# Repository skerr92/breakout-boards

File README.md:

# breakout-boards
Repository for various breakout board schematics, board files, and Bill of Materials

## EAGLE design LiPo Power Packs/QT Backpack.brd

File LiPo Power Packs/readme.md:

# power pack boards and schematics

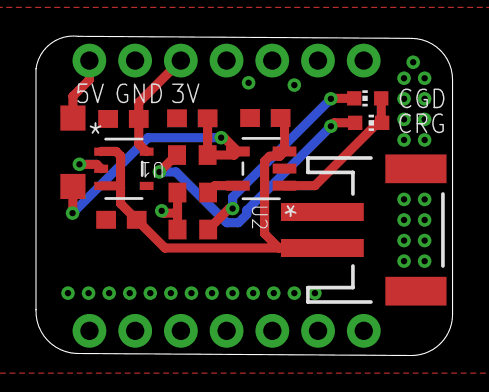
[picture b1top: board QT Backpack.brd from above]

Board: 2 copper layers, 23.1 x 17.8 mm, 15 parts (0 on the bottom side), 9 nets.

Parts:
C1: 0.47uF; C0603
C2: 1uF; C0603
C3, C4: 10uF; C0603
CGD: CHIP-LED0603
CRG: CHIP-LED0603
J1, J2: 1X07_NO_SILK
J3: JST-2-SMD
R1, R2: 470; R0603
R3: 2K; R0603
U1: TLV75533PDBVRDBV5_TEX-L; DBV5_TEX-L
U2: MCP73831T-2ACI/OT; SOT-23-5_MC
U$1: MBR0520LT1G; SOD3716X117(SOD-123)

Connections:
3V: C1.1, J1.5, U1.5
+5V: C4.1, R1.2, U2.4, U$1.2
GND: C1.2, C2.2, C3.2, C4.2, J1.6, J3.1, R2.1, R3.2, U1.2, U2.2
unnamed: R3.1, U2.5
unnamed: CGD.A, CRG.C, U2.1
unnamed: CGD.C, R2.2
unnamed: CRG.A, R1.1
VBAT: C2.1, C3.1, J3.2, U1.1, U1.3, U2.3
VUSB: J1.7, U$1.1

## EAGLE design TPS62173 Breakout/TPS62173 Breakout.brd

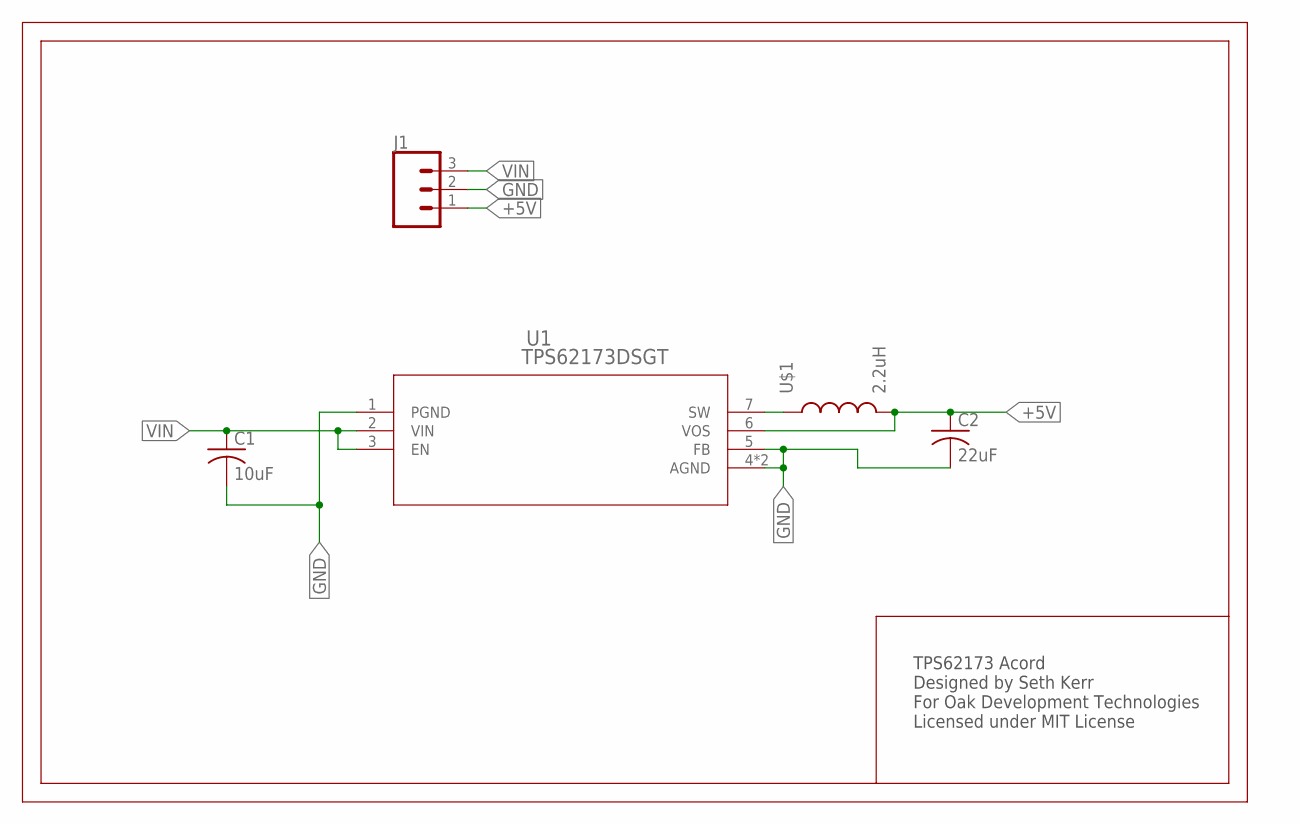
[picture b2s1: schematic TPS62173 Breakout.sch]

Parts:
C1: 10uF; C0603
C2: 22uF; C0603
J1: CONN_031X03_NO_SILK; 1X03_NO_SILK
U1: TPS62173DSGT; DSG8_1P6X0P9_TEX
U$1: 2.2uH; 2.7X3MM

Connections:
+5V: C2.1, J1.1, U1.6 (VOS), U$1.2
GND: C1.2, C2.2, J1.2, U1.1 (PGND), U1.4 (AGND), U1.5 (FB), U1.9 (AGND)
unnamed: U1.7 (SW), U$1.1
VIN: C1.1, J1.3, U1.2 (VIN), U1.3 (EN)

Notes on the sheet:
TPS62173 Acord Designed by Seth Kerr For Oak Development Technologies Licensed under MIT License

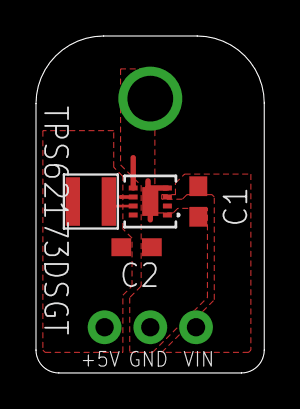
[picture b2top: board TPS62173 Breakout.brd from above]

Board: 2 copper layers, 12.7 x 18.7 mm, 5 parts (0 on the bottom side), 4 nets.

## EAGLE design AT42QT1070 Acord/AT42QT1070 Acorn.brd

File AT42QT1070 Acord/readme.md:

# AT42QT1070 acord schematics and board files

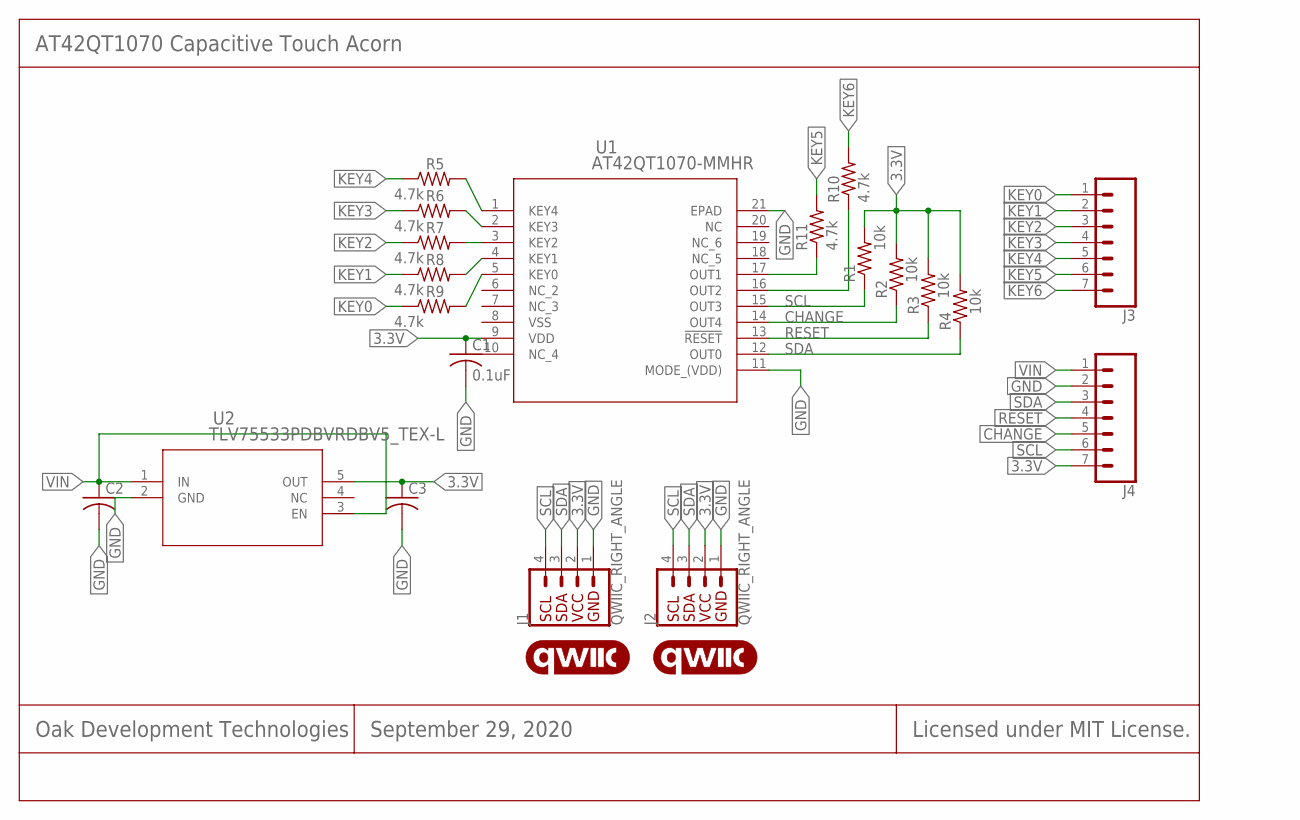
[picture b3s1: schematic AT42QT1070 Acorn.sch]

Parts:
C1: 0.1uF; C0402
C2, C3: C-USC0402; C0402
J1, J2: QWIIC_RIGHT_ANGLE; JST04_1MM_RA
J3, J4: CONN_07NO_SILK; 1X07_NO_SILK
LOGO1, LOGO2: QWIIC_LOGO_6MM; QWIIC_6MM
R1, R2, R3, R4: 10k; R0402
R5, R6, R7, R8, R9, R10, R11: 4.7k; R0402
U1: AT42QT1070-MMHR; VQFN20_3X3_MCH
U2: TLV75533PDBVRDBV5_TEX-L; DBV5_TEX-L

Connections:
3.3V: C1.1, C3.1, J1.2, J2.2, J4.7, R1.2, R2.2, R3.2, R4.2, U1.9 (VDD), U2.5 (OUT)
CHANGE: J4.5, R2.1, U1.14 (OUT4)
GND: C1.2, C2.2, C3.2, J1.1, J2.1, J4.2, U1.11 (MODE_(VDD)), U1.21 (EPAD), U2.2 (GND)
KEY0: J3.1, R9.1
KEY1: J3.2, R8.1
KEY2: J3.3, R7.1
KEY3: J3.4, R6.1
KEY4: J3.5, R5.1
KEY5: J3.6, R11.2
KEY6: J3.7, R10.2
unnamed: R11.1, U1.17 (OUT1)
unnamed: R10.1, U1.16 (OUT2)
unnamed: R5.2, U1.1 (KEY4)
unnamed: R6.2, U1.2 (KEY3)
unnamed: R7.2, U1.3 (KEY2)
unnamed: R8.2, U1.4 (KEY1)
unnamed: R9.2, U1.5 (KEY0)
RESET: J4.4, R3.1, U1.13 (!RESET)
SCL: J1.4, J2.4, J4.6, R1.1, U1.15 (OUT3)
SDA: J1.3, J2.3, J4.3, R4.1, U1.12 (OUT0)
VIN: C2.1, J4.1, U2.1 (IN), U2.3 (EN)

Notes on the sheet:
AT42QT1070 Capacitive Touch Acorn
Oak Development Technologies
Licensed under MIT License.
September 29, 2020

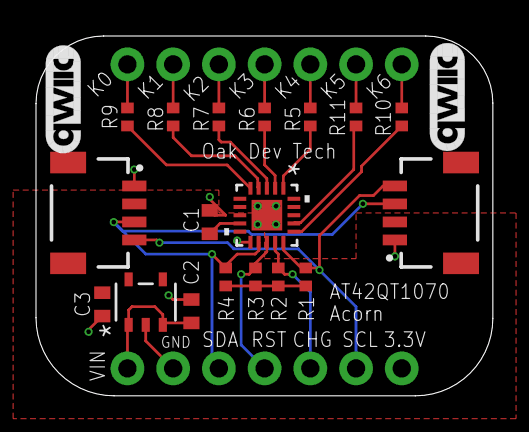
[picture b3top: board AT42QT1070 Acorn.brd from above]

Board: 2 copper layers, 25.4 x 20.0 mm, 22 parts (0 on the bottom side), 21 nets.

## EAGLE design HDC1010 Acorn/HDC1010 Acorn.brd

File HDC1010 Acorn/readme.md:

# HDC1010 Acorn

See MIT License in parent directory

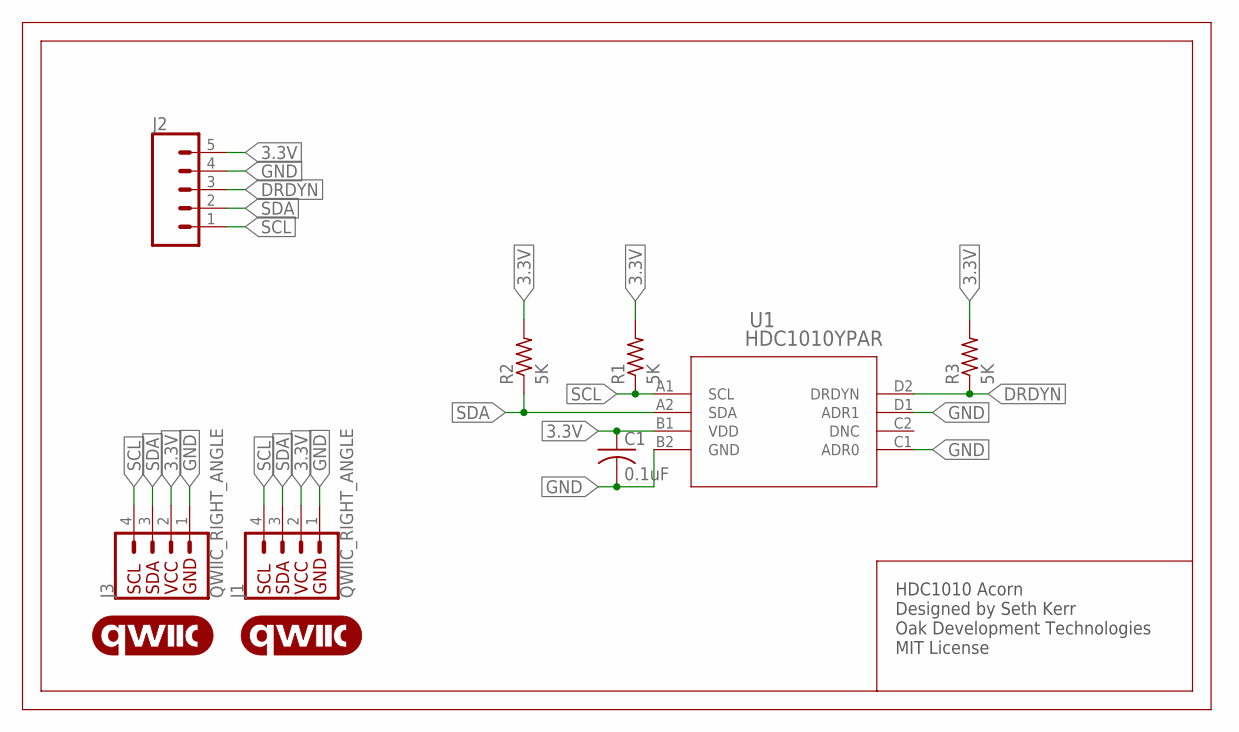
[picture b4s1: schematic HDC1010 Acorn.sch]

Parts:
C1: 0.1uF; C0402
J1, J3: QWIIC_RIGHT_ANGLE; JST04_1MM_RA
J2: CONN_05NO_SILK; 1X05_NO_SILK
LOGO1, LOGO2: QWIIC_LOGO_3MM; QWIIC_3MM
R1, R2, R3: 5K; R0603
U1: HDC1010YPAR; YPA8_TEX

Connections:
3.3V: C1.1, J1.2, J2.5, J3.2, R1.2, R2.2, R3.2, U1.B1 (VDD)
DRDYN: J2.3, R3.1, U1.D2 (DRDYN)
GND: C1.2, J1.1, J2.4, J3.1, U1.B2 (GND), U1.C1 (ADR0), U1.D1 (ADR1)
SCL: J1.4, J2.1, J3.4, R1.1, U1.A1 (SCL)
SDA: J1.3, J2.2, J3.3, R2.1, U1.A2 (SDA)

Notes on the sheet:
HDC1010 Acorn Designed by Seth Kerr Oak Development Technologies MIT License

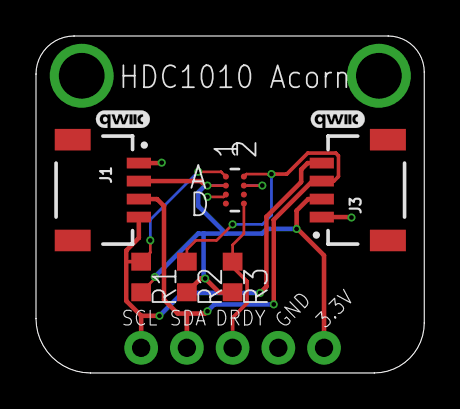
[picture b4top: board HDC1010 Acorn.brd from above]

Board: 2 copper layers, 21.6 x 18.7 mm, 10 parts (1 on the bottom side), 5 nets.

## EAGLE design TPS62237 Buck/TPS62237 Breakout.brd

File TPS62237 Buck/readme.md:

# TPS62237 3.3V Buck/Step Down converter board

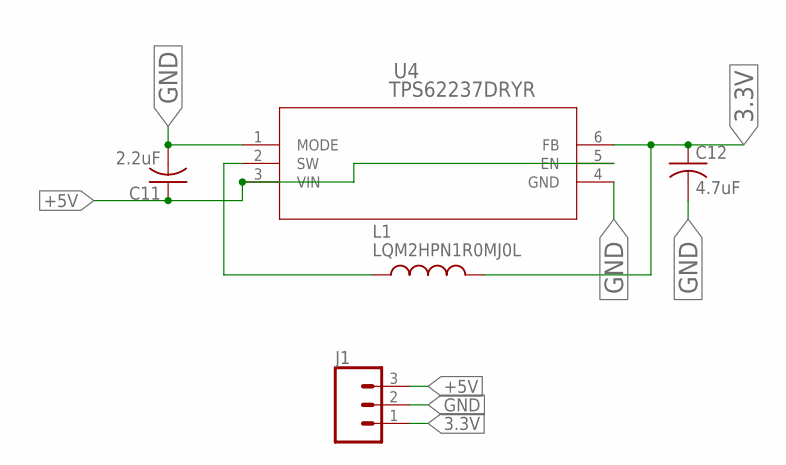
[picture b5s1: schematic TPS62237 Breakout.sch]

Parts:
C11: 2.2uF; C0603
C12: 4.7uF; C0603
J1: CONN_031X03_NO_SILK; 1X03_NO_SILK
L1: LQM2HPN1R0MJ0L; INDC2520X120N
U4: TPS62237DRYR; DRY6_TEX

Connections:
3.3V: C12.1, J1.1, L1.2, U4.6 (FB)
+5V: C11.1, J1.3, U4.3 (VIN), U4.5 (EN)
GND: C11.2, C12.2, J1.2, U4.1 (MODE), U4.4 (GND)
unnamed: L1.1, U4.2 (SW)

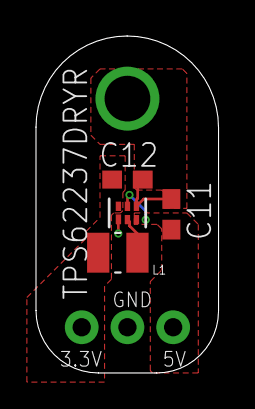
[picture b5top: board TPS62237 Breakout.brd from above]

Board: 2 copper layers, 10.1 x 18.7 mm, 5 parts (0 on the bottom side), 4 nets.

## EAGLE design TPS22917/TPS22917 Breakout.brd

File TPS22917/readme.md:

# TPS22917 Power Switch/ Load Switch IC breakout board.

Follow this <a href="https://www.oakdev.tech/tutorials-new-products/tutorial-getting-started-with-the-tps22917-load-switch-from-texas-instruments#/">LINK</a> to learn how to get started using this board.

# Buy the assembled board:

<a href="https://www.oakdev.tech/store/p1/TPS22917-Breakout.html#/">Buy the TPS22917 breakout here</a>

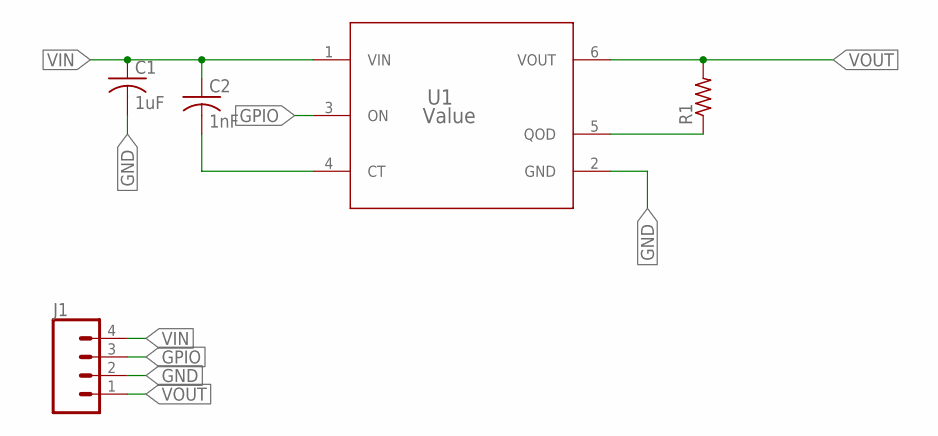
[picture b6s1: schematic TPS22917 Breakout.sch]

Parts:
C1: 1uF; C0603
C2: 1nF; C0603
J1: CONN_041X04_NO_SILK; 1X04_NO_SILK
R1: R-US_R0603; R0603
U1: Value; DBV0006_L

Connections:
GND: C1.2, J1.2, U1.2 (GND)
GPIO: J1.3, U1.3 (ON)
unnamed: C2.2, U1.4 (CT)
unnamed: R1.1, U1.5 (QOD)
VIN: C1.1, C2.1, J1.4, U1.1 (VIN)
VOUT: J1.1, R1.2, U1.6 (VOUT)

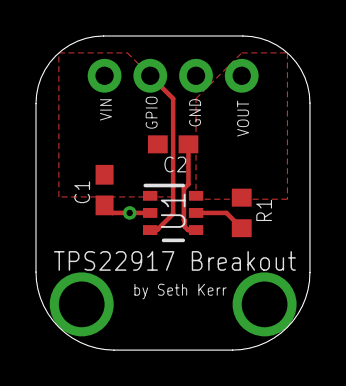
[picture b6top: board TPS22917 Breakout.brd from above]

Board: 2 copper layers, 15.2 x 17.4 mm, 5 parts (0 on the bottom side), 6 nets.

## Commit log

2020-08-28 Create example.ino
    making an example implementation using arduino code
2020-08-31 Create example.py
    adding an example for use with circuit python
2020-09-01 Update LICENSE
    updating to include hardware associated on this repository.
2020-09-03 Update example.py
    fixing some syntax errors
2020-09-03 Update example.py
    forgot analogy imports
2020-09-07 Create tutorial.ino
    Adding the tutorial code from the Oak Dev Tech site.
2020-09-07 Update readme.md
    updating the readme with some links.
2020-10-22 Add files via upload
    adding qt backpack schematic and board files
2020-10-22 Create AT42QT1070 Acorn
2020-10-22 Add files via upload
    updating board files
2020-12-09 Add files via upload
    making sure current files are up to date.
2020-12-09 Delete QT Backpack.brd
    opps add
2020-12-09 Delete QT Backpack.sch
    another opps add
2020-12-09 Add files via upload
    PDF Schematic
2021-07-30 Fix AT42QT1070 directory name
2021-07-31 Adding some examples to AT42QT board
2022-03-22 adding latest and JLCPCB CAM for 10pc panel

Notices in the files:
parts and their libraries:
SparkFun-Connectors: Licensing: Creative Commons ShareAlike 4.0 International - https://creativecommons.org/licenses/by-sa/4.0
COPYRIGHT: Copyright (C) 2018 Accelerated Designs. All rights reserved
